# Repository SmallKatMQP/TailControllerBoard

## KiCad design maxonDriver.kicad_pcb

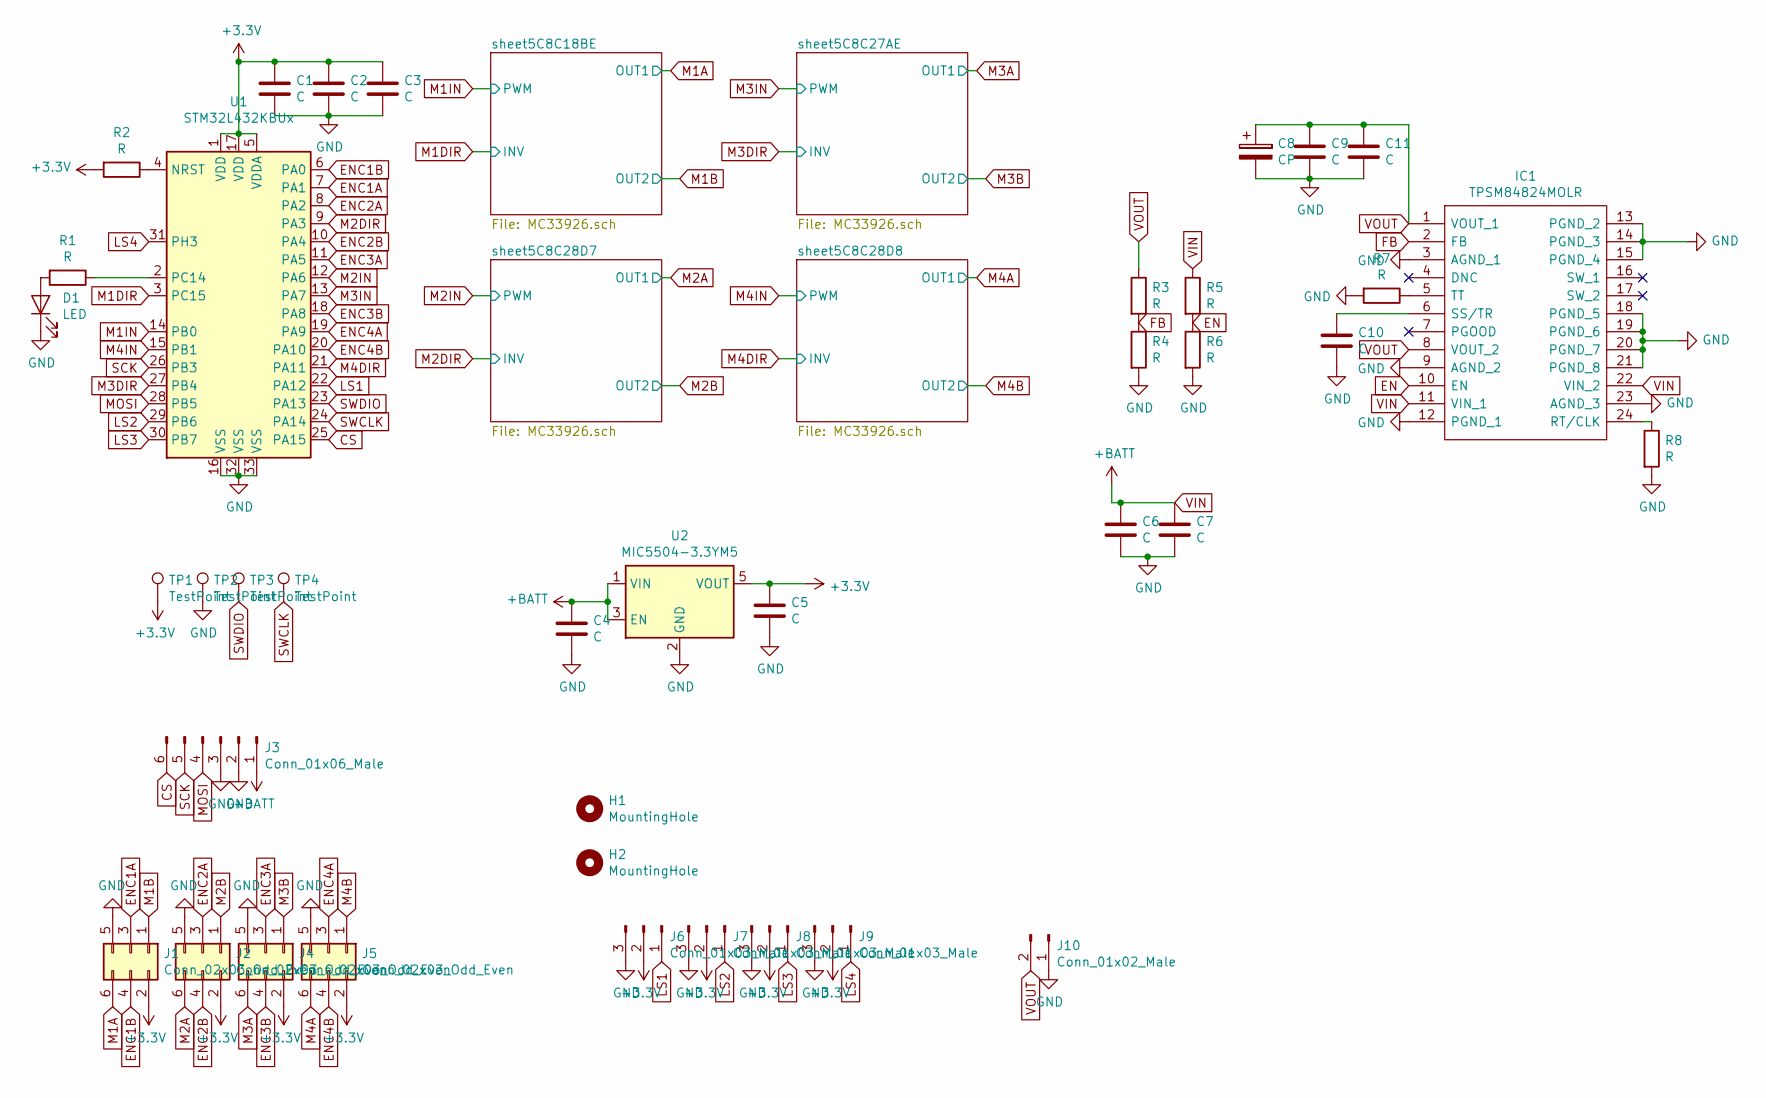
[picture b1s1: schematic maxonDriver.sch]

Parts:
C1, C2, C3, C4, C5, C10: C; C_0402_1005Metric
C6, C7, C9, C11: C; C_0805_2012Metric
C8: CP; CP_Elec_4x3
D1: LED; LED_0603_1608Metric
H1, H2: MountingHole; MountingHole_2.2mm_M2
IC1: TPSM84824MOLR; TPSM84624MOLR; Manufacturer_Part_Number TPSM84824MOLR; Mouser Part Number 595-TPSM84824MOLR
J1, J2, J4, J5: Conn_02x03_Odd_Even; PinHeader_2x03_P2.54mm_Vertical
J3: Conn_01x06_Male; Molex_CLIK-Mate_502443-0670_1x06-1MP_P2.00mm_Vertical
J6, J7, J8, J9: Conn_01x03_Male; PinSocket_1x03_P2.54mm_Vertical
J10: Conn_01x02_Male; Molex_CLIK-Mate_502443-0270_1x02-1MP_P2.00mm_Vertical
R1, R2, R3, R4, R5, R6, R7, R8: R; R_0402_1005Metric
TP1, TP2, TP3, TP4: TestPoint; TestPoint_Pad_D1.5mm
U1: STM32L432KBUx; QFN-32-1EP_5x5mm_P0.5mm_EP3.45x3.45mm
U2: MIC5504-3.3YM5; SOT-23-5

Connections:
+3V3: C1.1, C2.1, C3.1, C5.1, J1.2, J2.2, J4.2, J5.2, J6.2, J7.2, J8.2, J9.2, R2.2, TP1.1, U1.1 (VDD), U1.5 (VDDA), U1.17 (VDD), U2.5 (VOUT); also elsewhere on the board
CS: J3.6, U1.25 (PA15)
EN: IC1.10 (EN), R5.2, R6.1
ENC1A: J1.3, U1.7 (PA1)
ENC1B: J1.4, U1.6 (PA0)
ENC2A: J2.3, U1.8 (PA2)
ENC2B: J2.4, U1.10 (PA4)
ENC3A: J4.3, U1.11 (PA5)
ENC3B: J4.4, U1.18 (PA8)
ENC4A: J5.3, U1.19 (PA9)
ENC4B: J5.4, U1.20 (PA10)
FB: IC1.2 (FB), R3.2, R4.1
GND: C1.2, C2.2, C3.2, C4.2, C5.2, C6.2, C7.2, C8.2, C9.2, C10.2, C11.2, D1.1 (K), IC1.3 (AGND_1), IC1.9 (AGND_2), IC1.12 (PGND_1), IC1.13 (PGND_2), IC1.14 (PGND_3), IC1.15 (PGND_4), IC1.18 (PGND_5), IC1.19 (PGND_6), IC1.20 (PGND_7), IC1.21 (PGND_8), IC1.23 (AGND_3), J1.5, J2.5, J3.2, J3.3, J4.5, J5.5, J6.3, J7.3, J8.3, J9.3, J10.1, R4.2, R6.2, R7.2, R8.2, TP2.1, U1.16 (VSS), U1.32 (VSS), U1.33 (VSS), U2.2 (GND); also elsewhere on the board
LS1: J6.1, U1.22 (PA12)
LS2: J7.1, U1.29 (PB6)
LS3: J8.1, U1.30 (PB7)
LS4: J9.1, U1.31 (PH3)
M1A: J1.6; also elsewhere on the board
M1B: J1.1; also elsewhere on the board
M1DIR: U1.3 (PC15); also elsewhere on the board
M1IN: U1.14 (PB0); also elsewhere on the board
M2A: J2.6; also elsewhere on the board
M2B: J2.1; also elsewhere on the board
M2DIR: U1.9 (PA3); also elsewhere on the board
M2IN: U1.12 (PA6); also elsewhere on the board
M3A: J4.6; also elsewhere on the board
M3B: J4.1; also elsewhere on the board
M3DIR: U1.27 (PB4); also elsewhere on the board
M3IN: U1.13 (PA7); also elsewhere on the board
M4A: J5.6; also elsewhere on the board
M4B: J5.1; also elsewhere on the board
M4DIR: U1.21 (PA11); also elsewhere on the board
M4IN: U1.15 (PB1); also elsewhere on the board
MOSI: J3.4, U1.28 (PB5)
unnamed: C10.1, IC1.6 (SS/TR)
unnamed: D1.2 (A), R1.2
unnamed: IC1.5 (TT), R7.1
unnamed: IC1.24 (RT/CLK), R8.1
unnamed: R1.1, U1.2 (PC14)
unnamed: R2.1, U1.4 (NRST)
SCK: J3.5, U1.26 (PB3)
SWCLK: TP4.1, U1.24 (PA14)
SWDIO: TP3.1, U1.23 (PA13)
VIN: C4.1, C6.1, C7.1, IC1.11 (VIN_1), IC1.22 (VIN_2), J3.1, R5.1, U2.1 (VIN), U2.3 (EN); also elsewhere on the board
VOUT: C8.1, C9.1, C11.1, IC1.1 (VOUT_1), IC1.8 (VOUT_2), J10.2, R3.1

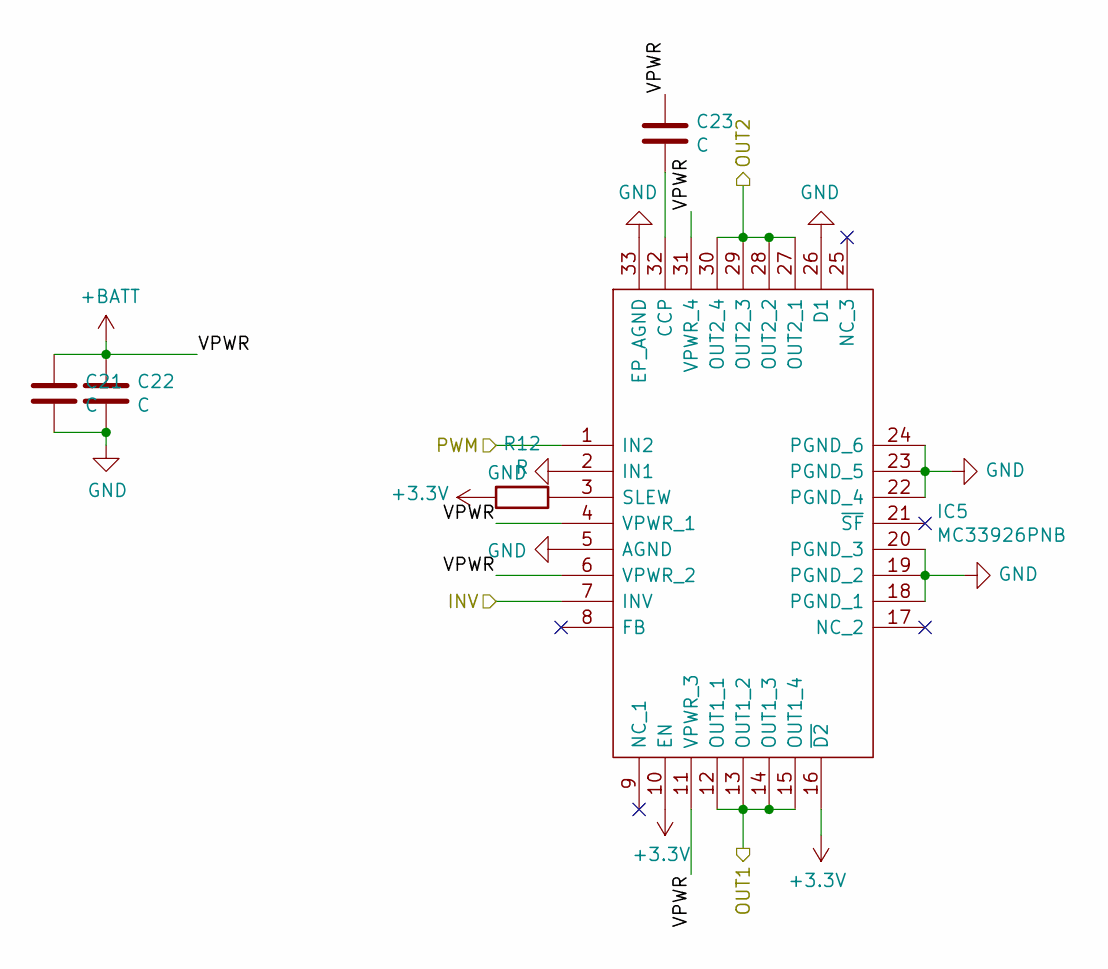
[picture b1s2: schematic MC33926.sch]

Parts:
C12, C14: C; C_0402_1005Metric
C13: C; C_1210_3225Metric
IC2: MC33926PNB; QFN80P800X800X220-33N; Manufacturer_Part_Number MC33926PNB
R9: R; R_0402_1005Metric

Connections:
+3V3: IC2.10 (EN), IC2.16 (~D2), R9.2; also elsewhere on the board
GND: C12.2, C13.2, IC2.2 (IN1), IC2.5 (AGND), IC2.18 (PGND_1), IC2.19 (PGND_2), IC2.20 (PGND_3), IC2.22 (PGND_4), IC2.23 (PGND_5), IC2.24 (PGND_6), IC2.26 (D1), IC2.33 (EP_AGND); also elsewhere on the board
M1A: IC2.12 (OUT1_1), IC2.13 (OUT1_2), IC2.14 (OUT1_3), IC2.15 (OUT1_4); also elsewhere on the board
M1B: IC2.27 (OUT2_1), IC2.28 (OUT2_2), IC2.29 (OUT2_3), IC2.30 (OUT2_4); also elsewhere on the board
M1DIR: IC2.7 (INV); also elsewhere on the board
M1IN: IC2.1 (IN2); also elsewhere on the board
unnamed: C14.2, IC2.32 (CCP)
unnamed: IC2.3 (SLEW), R9.1
VIN: C12.1, C13.1, C14.1, IC2.4 (VPWR_1), IC2.6 (VPWR_2), IC2.11 (VPWR_3), IC2.31 (VPWR_4); also elsewhere on the board

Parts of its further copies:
C15, C17, C18, C20, C21, C23: C; C_0402_1005Metric
C16, C19, C22: C; C_1210_3225Metric
IC3, IC4, IC5: MC33926PNB; QFN80P800X800X220-33N; Manufacturer_Part_Number MC33926PNB
R10, R11, R12: R; R_0402_1005Metric

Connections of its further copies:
+3V3: IC3.10 (EN), IC3.16 (~D2), IC4.10 (EN), IC4.16 (~D2), IC5.10 (EN), IC5.16 (~D2), R10.2, R11.2, R12.2; also elsewhere on the board
GND: C15.2, C16.2, C18.2, C19.2, C21.2, C22.2, IC3.2 (IN1), IC3.5 (AGND), IC3.18 (PGND_1), IC3.19 (PGND_2), IC3.20 (PGND_3), IC3.22 (PGND_4), IC3.23 (PGND_5), IC3.24 (PGND_6), IC3.26 (D1), IC3.33 (EP_AGND), IC4.2 (IN1), IC4.5 (AGND), IC4.18 (PGND_1), IC4.19 (PGND_2), IC4.20 (PGND_3), IC4.22 (PGND_4), IC4.23 (PGND_5), IC4.24 (PGND_6), IC4.26 (D1), IC4.33 (EP_AGND), IC5.2 (IN1), IC5.5 (AGND), IC5.18 (PGND_1), IC5.19 (PGND_2), IC5.20 (PGND_3), IC5.22 (PGND_4), IC5.23 (PGND_5), IC5.24 (PGND_6), IC5.26 (D1), IC5.33 (EP_AGND); also elsewhere on the board
M2A: IC4.12 (OUT1_1), IC4.13 (OUT1_2), IC4.14 (OUT1_3), IC4.15 (OUT1_4); also elsewhere on the board
M2B: IC4.27 (OUT2_1), IC4.28 (OUT2_2), IC4.29 (OUT2_3), IC4.30 (OUT2_4); also elsewhere on the board
M2DIR: IC4.7 (INV); also elsewhere on the board
M2IN: IC4.1 (IN2); also elsewhere on the board
M3A: IC3.12 (OUT1_1), IC3.13 (OUT1_2), IC3.14 (OUT1_3), IC3.15 (OUT1_4); also elsewhere on the board
M3B: IC3.27 (OUT2_1), IC3.28 (OUT2_2), IC3.29 (OUT2_3), IC3.30 (OUT2_4); also elsewhere on the board
M3DIR: IC3.7 (INV); also elsewhere on the board
M3IN: IC3.1 (IN2); also elsewhere on the board
M4A: IC5.12 (OUT1_1), IC5.13 (OUT1_2), IC5.14 (OUT1_3), IC5.15 (OUT1_4); also elsewhere on the board
M4B: IC5.27 (OUT2_1), IC5.28 (OUT2_2), IC5.29 (OUT2_3), IC5.30 (OUT2_4); also elsewhere on the board
M4DIR: IC5.7 (INV); also elsewhere on the board
M4IN: IC5.1 (IN2); also elsewhere on the board
unnamed: C17.2, IC3.32 (CCP)
unnamed: C20.2, IC4.32 (CCP)
unnamed: C23.2, IC5.32 (CCP)
unnamed: IC3.3 (SLEW), R10.1
unnamed: IC4.3 (SLEW), R11.1
unnamed: IC5.3 (SLEW), R12.1
VIN: C15.1, C16.1, C17.1, C18.1, C19.1, C20.1, C21.1, C22.1, C23.1, IC3.4 (VPWR_1), IC3.6 (VPWR_2), IC3.11 (VPWR_3), IC3.31 (VPWR_4), IC4.4 (VPWR_1), IC4.6 (VPWR_2), IC4.11 (VPWR_3), IC4.31 (VPWR_4), IC5.4 (VPWR_1), IC5.6 (VPWR_2), IC5.11 (VPWR_3), IC5.31 (VPWR_4); also elsewhere on the board

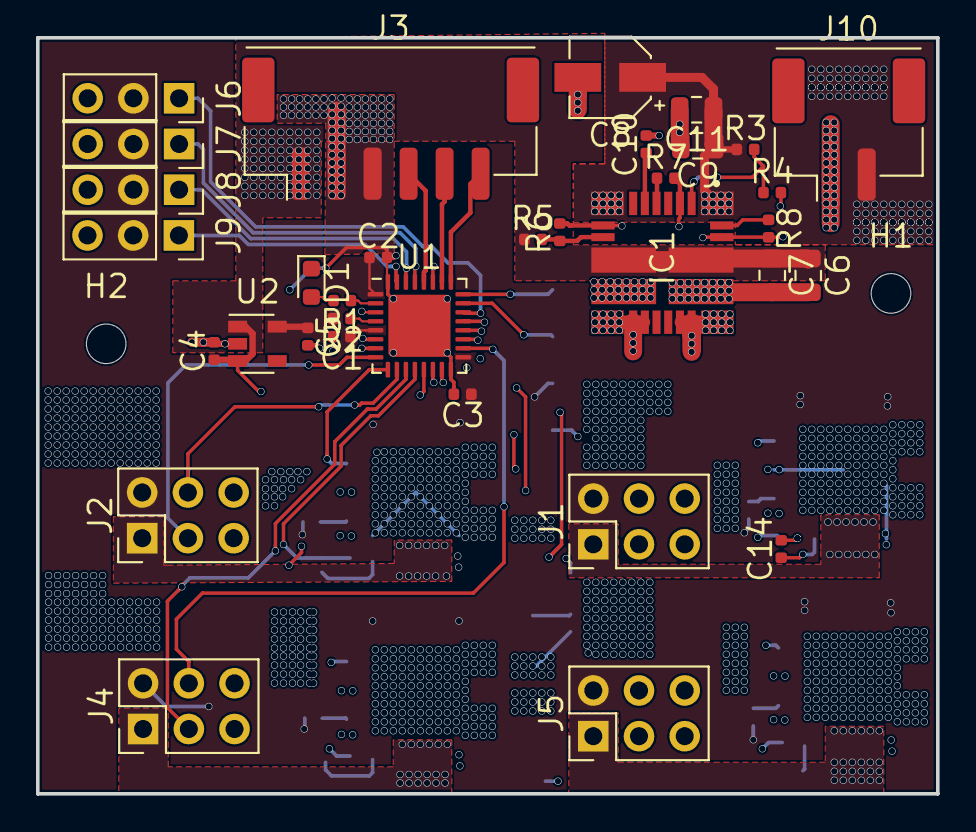
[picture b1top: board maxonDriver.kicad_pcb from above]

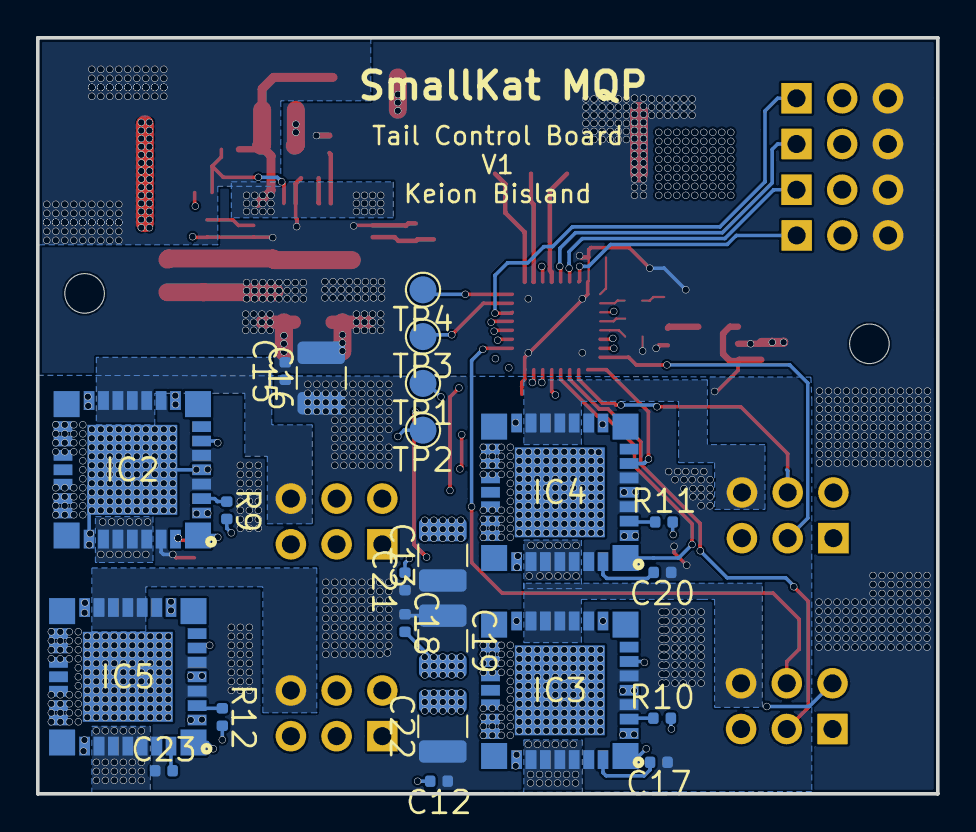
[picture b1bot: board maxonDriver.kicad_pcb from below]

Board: 4 copper layers, 50.0 x 42.0 mm, 59 parts (23 on the bottom side), 53 nets.

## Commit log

2019-03-16 Rev1 Complete
